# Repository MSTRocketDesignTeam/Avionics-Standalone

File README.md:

# Avionics-Standalone-PCB
Standalone Avionics Board

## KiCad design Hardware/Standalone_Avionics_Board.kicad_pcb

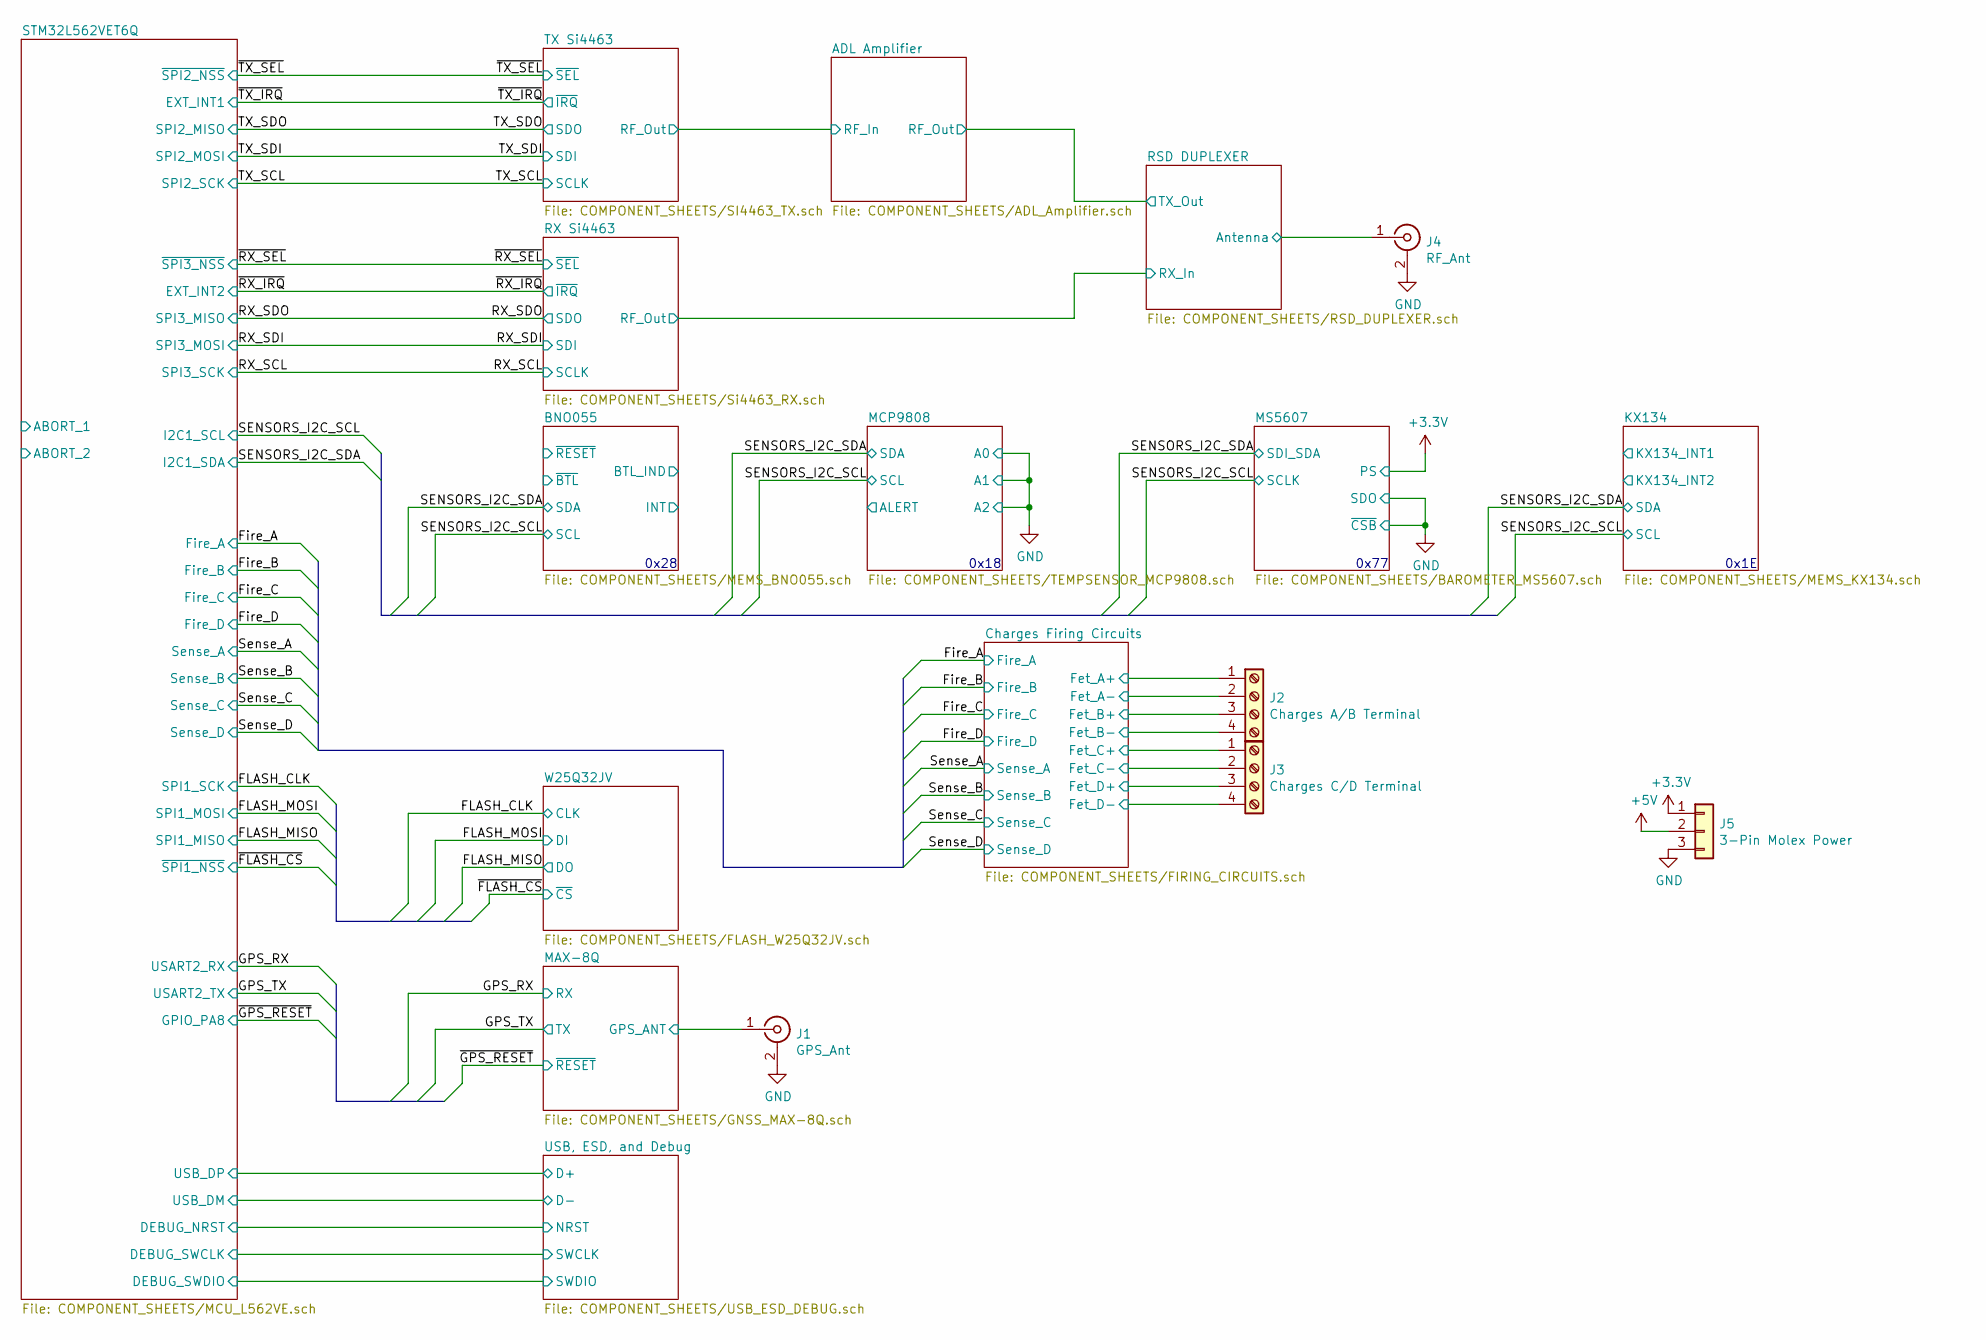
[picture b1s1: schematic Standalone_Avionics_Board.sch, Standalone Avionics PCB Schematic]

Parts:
J1: GPS_Ant; SMA_Amphenol_132134-11_Vertical
J2: Charges A/B Terminal; TerminalBlock_Phoenix_MKDS-1,5-4_1x04_P5.00mm_Horizontal
J3: Charges C/D Terminal; TerminalBlock_Phoenix_MKDS-1,5-4_1x04_P5.00mm_Horizontal
J4: RF_Ant; SMA_Amphenol_132134-11_Vertical
J5: 3-Pin Molex Power; Molex_KK-254_AE-6410-03A_1x03_P2.54mm_Vertical

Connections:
+3V3: J5.1; also elsewhere on the board
+5V: J5.2; also elsewhere on the board
/Charges Firing Circuits/Fet_A+: J2.1; also elsewhere on the board
/Charges Firing Circuits/Fet_A-: J2.2; also elsewhere on the board
/Charges Firing Circuits/Fet_B+: J2.3; also elsewhere on the board
/Charges Firing Circuits/Fet_B-: J2.4; also elsewhere on the board
/Charges Firing Circuits/Fet_C+: J3.1; also elsewhere on the board
/Charges Firing Circuits/Fet_C-: J3.2; also elsewhere on the board
/Charges Firing Circuits/Fet_D+: J3.3; also elsewhere on the board
/Charges Firing Circuits/Fet_D-: J3.4; also elsewhere on the board
/MAX-8Q/GPS_ANT: J1.1 (In); also elsewhere on the board
/RSD DUPLEXER/Antenna: J4.1 (In); also elsewhere on the board
GND: J1.2 (Ext), J4.2 (Ext), J5.3; also elsewhere on the board

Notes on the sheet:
0x1E
0x77
0x18
0x28

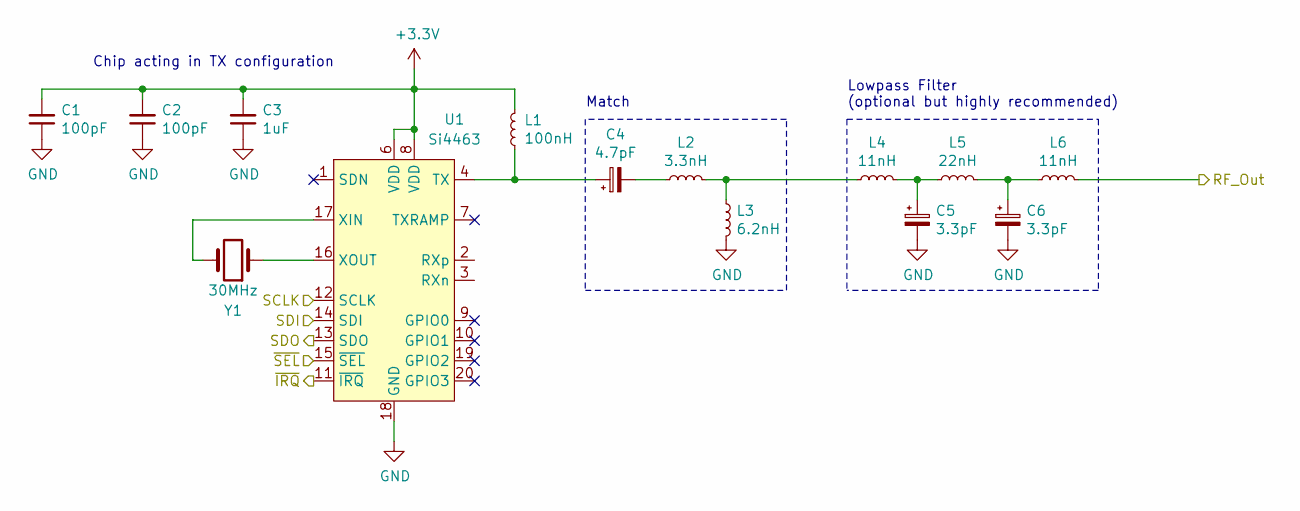
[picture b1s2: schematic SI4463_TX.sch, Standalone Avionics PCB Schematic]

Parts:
C1, C2: 100pF; C_0402_1005Metric
C3: 1uF; C_0402_1005Metric
C4: 4.7pF; C_0402_1005Metric
C5, C6: 3.3pF; C_0402_1005Metric
L1: 100nH; L_0402_1005Metric
L2: 3.3nH; L_0402_1005Metric
L3: 6.2nH; L_0402_1005Metric
L4, L6: 11nH; L_0402_1005Metric
L5: 22nH; L_0402_1005Metric
U1: Si4463; QFN-20-1EP_4x4mm_P0.5mm_EP2.5x2.5mm
Y1: 30MHz; Crystal_SMD_0603-2Pin_6.0x3.5mm

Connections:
+3V3: C1.2, C2.2, C3.2, L1.2, U1.6 (VDD), U1.8 (VDD); also elsewhere on the board
/ADL Amplifier/RF_In: L6.2; also elsewhere on the board
/TX_SCL: U1.12 (SCLK); also elsewhere on the board
/TX_SDI: U1.14 (SDI); also elsewhere on the board
/TX_SDO: U1.13 (SDO); also elsewhere on the board
/~TX_IRQ: U1.11 (~IRQ); also elsewhere on the board
/~TX_SEL: U1.15 (~SEL); also elsewhere on the board
GND: C1.1, C2.1, C3.1, C5.2, C6.2, L3.2, U1.18 (GND), U1.21 (GND); also elsewhere on the board
unnamed: C4.1, L1.1, U1.4 (TX)
unnamed: C4.2, L2.1
unnamed: C5.1, L4.2, L5.1
unnamed: C6.1, L5.2, L6.1
unnamed: L2.2, L3.1, L4.1
unnamed: U1.16 (XOUT), Y1.1
unnamed: U1.17 (XIN), Y1.2

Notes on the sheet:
Chip acting in TX configuration
Lowpass Filter (optional but highly recommended)
Match

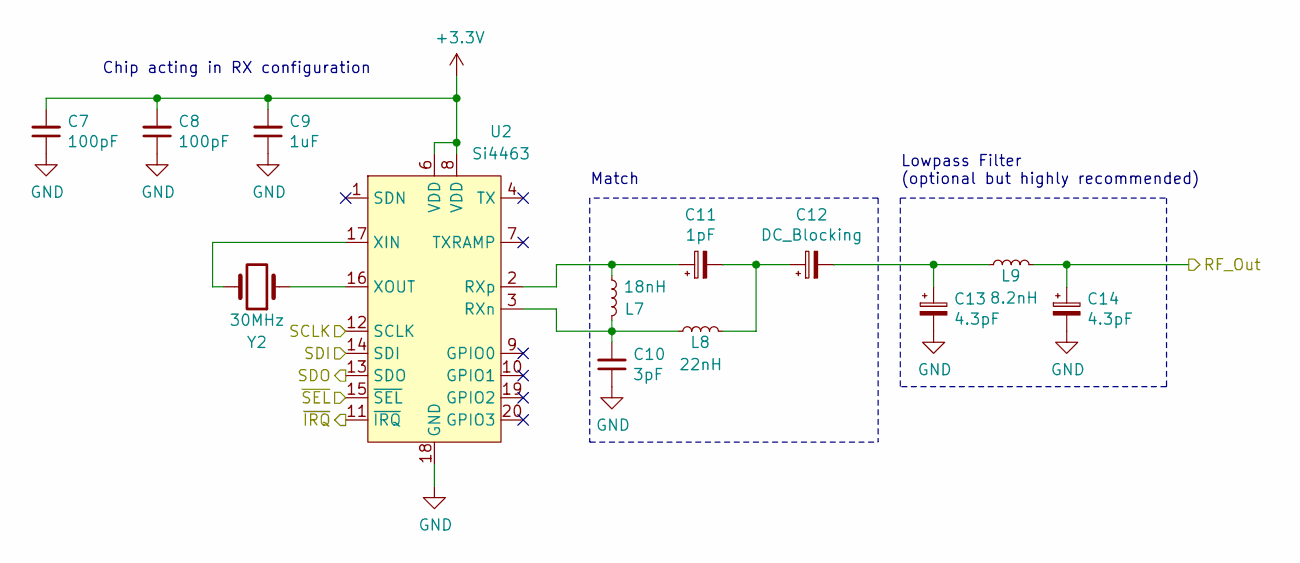
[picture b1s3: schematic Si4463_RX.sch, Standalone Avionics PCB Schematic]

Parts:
C7, C8: 100pF; C_0402_1005Metric
C9: 1uF; C_0402_1005Metric
C10: 3pF; C_0402_1005Metric
C11: 1pF; C_0402_1005Metric
C12: DC_Blocking; C_0402_1005Metric
C13, C14: 4.3pF; C_0402_1005Metric
L7: 18nH; L_0402_1005Metric
L8: 22nH; L_0402_1005Metric
L9: 8.2nH; L_0402_1005Metric
U2: Si4463; QFN-20-1EP_4x4mm_P0.5mm_EP2.5x2.5mm
Y2: 30MHz; Crystal_SMD_0603-2Pin_6.0x3.5mm

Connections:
+3V3: C7.2, C8.2, C9.2, U2.6 (VDD), U2.8 (VDD); also elsewhere on the board
/RX Si4463/RF_Out: C14.1, L9.2; also elsewhere on the board
/RX_SCL: U2.12 (SCLK); also elsewhere on the board
/RX_SDI: U2.14 (SDI); also elsewhere on the board
/RX_SDO: U2.13 (SDO); also elsewhere on the board
/~RX_IRQ: U2.11 (~IRQ); also elsewhere on the board
/~RX_SEL: U2.15 (~SEL); also elsewhere on the board
GND: C7.1, C8.1, C9.1, C10.1, C13.2, C14.2, U2.18 (GND), U2.21 (GND); also elsewhere on the board
unnamed: C10.2, L7.2, L8.1, U2.3 (RXn)
unnamed: C11.1, L7.1, U2.2 (RXp)
unnamed: C11.2, C12.1, L8.2
unnamed: C12.2, C13.1, L9.1
unnamed: U2.16 (XOUT), Y2.1
unnamed: U2.17 (XIN), Y2.2

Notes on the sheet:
Chip acting in RX configuration
Lowpass Filter (optional but highly recommended)
Match

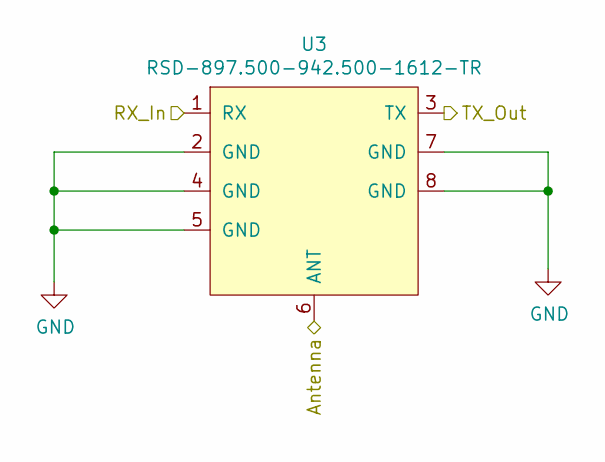
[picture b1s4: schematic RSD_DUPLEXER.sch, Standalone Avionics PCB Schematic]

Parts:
U3: RSD-897.500-942.500-1612-TR

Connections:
/ADL Amplifier/RF_Out: U3.3 (TX); also elsewhere on the board
/RSD DUPLEXER/Antenna: U3.6 (ANT); also elsewhere on the board
/RX Si4463/RF_Out: U3.1 (RX); also elsewhere on the board
GND: U3.2 (GND), U3.4 (GND), U3.5 (GND), U3.7 (GND), U3.8 (GND); also elsewhere on the board

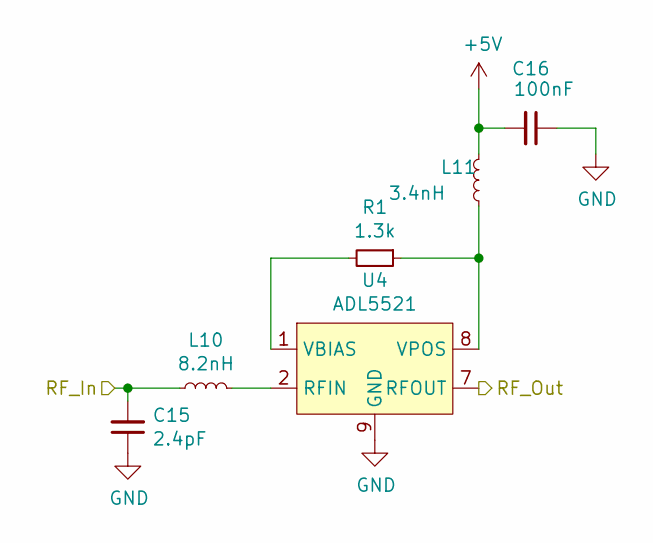
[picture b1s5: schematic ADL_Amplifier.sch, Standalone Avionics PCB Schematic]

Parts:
C15: 2.4pF; C_0402_1005Metric
C16: 100nF; C_0402_1005Metric
L10: 8.2nH; L_0402_1005Metric
L11: 3.4nH; L_0402_1005Metric
R1: 1.3k; R_0402_1005Metric
U4: ADL5521; LFCSP-8-1EP_3x2mm_P0.5mm_EP1.6x1.65mm

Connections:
+5V: C16.2, L11.2; also elsewhere on the board
/ADL Amplifier/RF_In: C15.2, L10.1; also elsewhere on the board
/ADL Amplifier/RF_Out: U4.7 (RFOUT); also elsewhere on the board
GND: C15.1, C16.1, U4.9 (GND); also elsewhere on the board
unnamed: L10.2, U4.2 (RFIN)
unnamed: L11.1, R1.1, U4.8 (VPOS)
unnamed: R1.2, U4.1 (VBIAS)

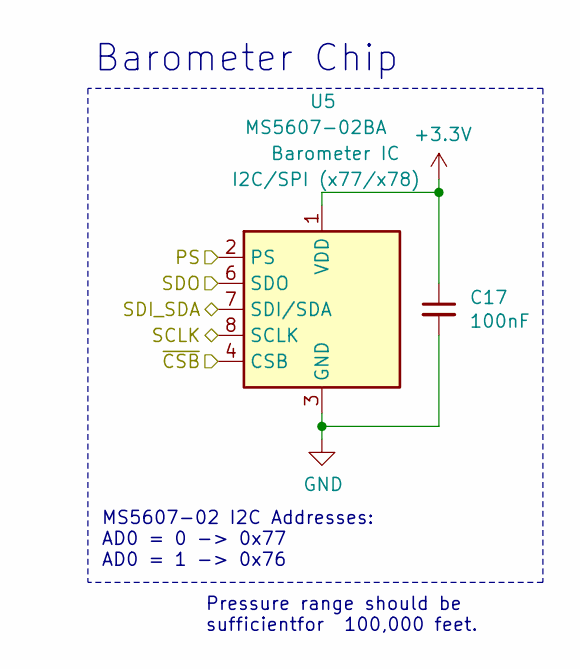
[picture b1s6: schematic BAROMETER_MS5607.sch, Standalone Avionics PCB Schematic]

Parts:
C17: 100nF; C_0402_1005Metric
U5: MS5607-02BA; LGA-8_3x5mm_P1.25mm

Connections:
+3V3: C17.1, U5.1 (VDD), U5.2 (PS); also elsewhere on the board
/SENSORS_I2C_SCL: U5.8 (SCLK); also elsewhere on the board
/SENSORS_I2C_SDA: U5.7 (SDI/SDA); also elsewhere on the board
GND: C17.2, U5.3 (GND), U5.4 (CSB), U5.5 (CSB), U5.6 (SDO); also elsewhere on the board

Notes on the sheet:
Barometer Chip
MS5607-02 I2C Addresses: AD0 = 0 -> 0x77 AD0 = 1 -> 0x76
Pressure range should be sufficientfor ~ 100,000 feet.

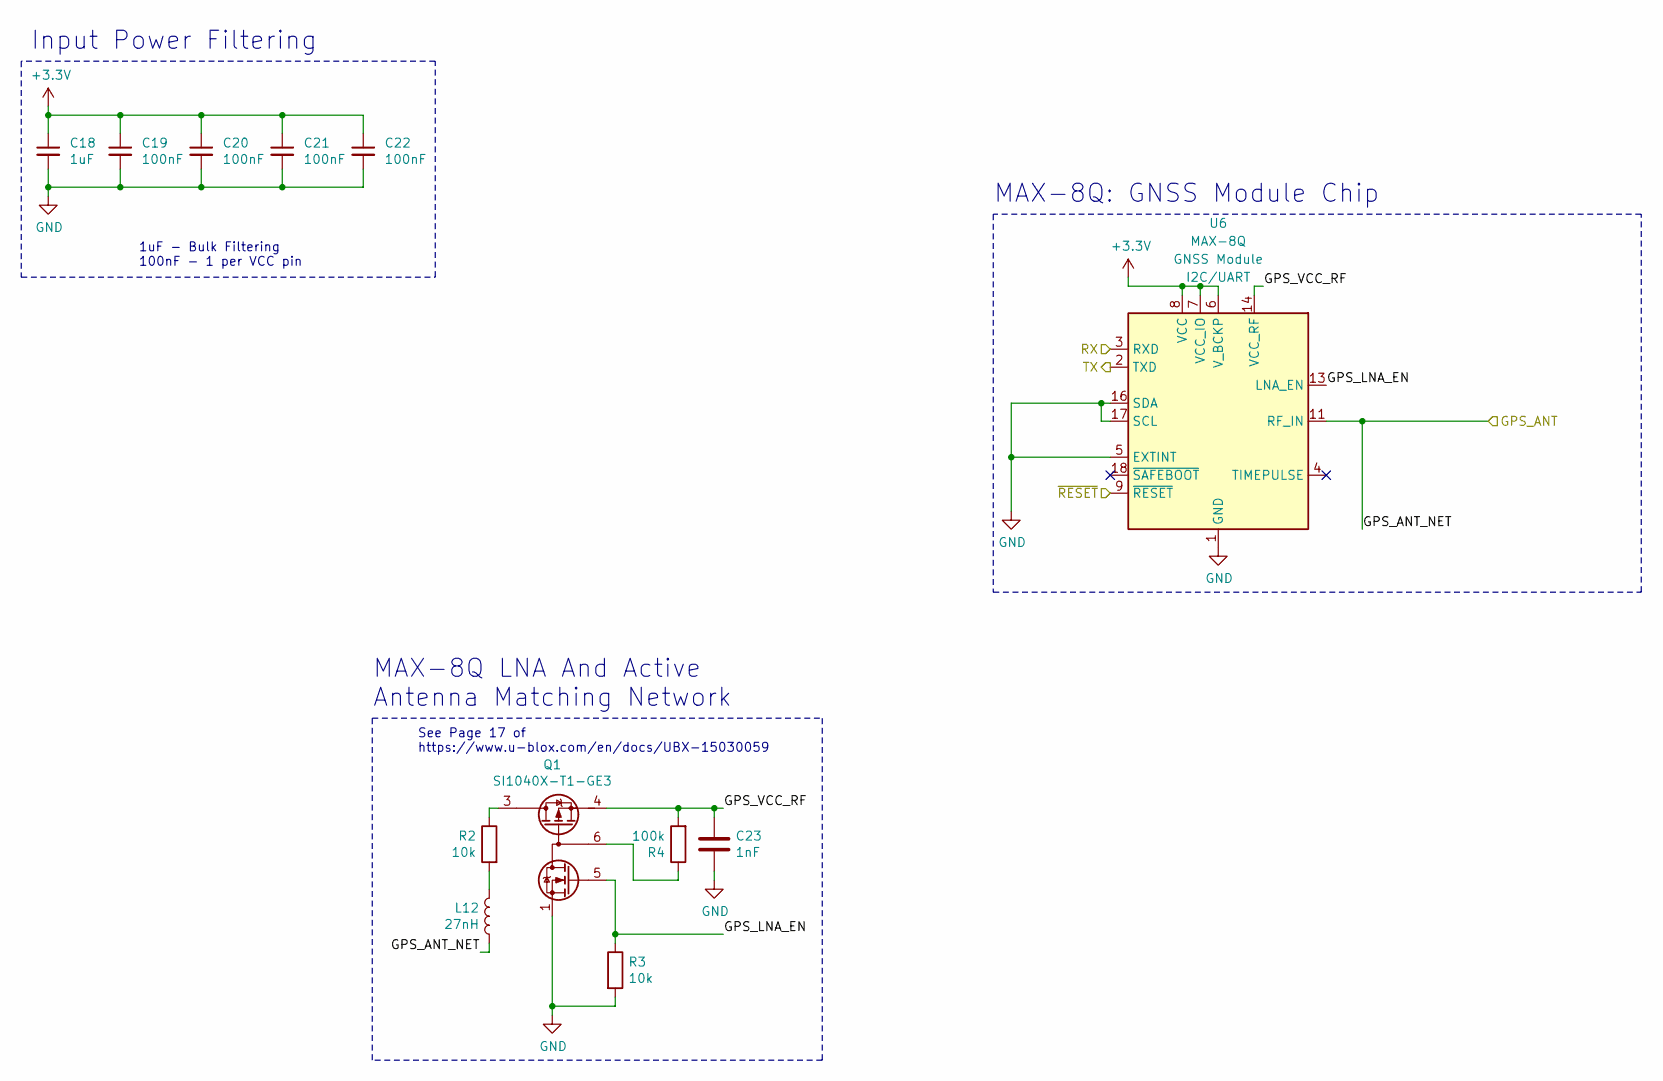
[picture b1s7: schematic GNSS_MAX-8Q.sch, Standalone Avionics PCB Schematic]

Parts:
C18: 1uF; C_0402_1005Metric
C19, C20, C21, C22: 100nF; C_0402_1005Metric
C23: 1nF; C_0402_1005Metric
L12: 27nH; L_0402_1005Metric
Q1: SI1040X-T1-GE3; SOT-563
R2, R3: 10k; R_0402_1005Metric
R4: 100k; R_0402_1005Metric
U6: MAX-8Q; ublox_MAX

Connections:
+3V3: C18.1, C19.1, C20.1, C21.1, C22.1, U6.6 (V_BCKP), U6.7 (VCC_IO), U6.8 (VCC); also elsewhere on the board
/GPS_RX: U6.3 (RXD); also elsewhere on the board
/GPS_TX: U6.2 (TXD); also elsewhere on the board
/MAX-8Q/GPS_ANT: L12.2, U6.11 (RF_IN); also elsewhere on the board
/MAX-8Q/GPS_LNA_EN: Q1.5 (G1), R3.1, U6.13 (LNA_EN)
/MAX-8Q/GPS_VCC_RF: C23.1, Q1.4 (S2), R4.2, U6.14 (VCC_RF)
/~GPS_RESET: U6.9 (~RESET); also elsewhere on the board
GND: C18.2, C19.2, C20.2, C21.2, C22.2, C23.2, Q1.1 (S1), R3.2, U6.1 (GND), U6.5 (EXTINT), U6.10 (GND), U6.12 (GND), U6.16 (SDA), U6.17 (SCL); also elsewhere on the board
unnamed: L12.1, R2.2
unnamed: Q1.2 (D2), Q1.3 (D2), R2.1
unnamed: Q1.6 (D1), R4.1

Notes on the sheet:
See Page 17 of https://www.u-blox.com/en/docs/UBX-15030059
MAX-8Q: GNSS Module Chip
1uF - Bulk Filtering 100nF - 1 per VCC pin
Input Power Filtering
MAX-8Q LNA And Active Antenna Matching Network

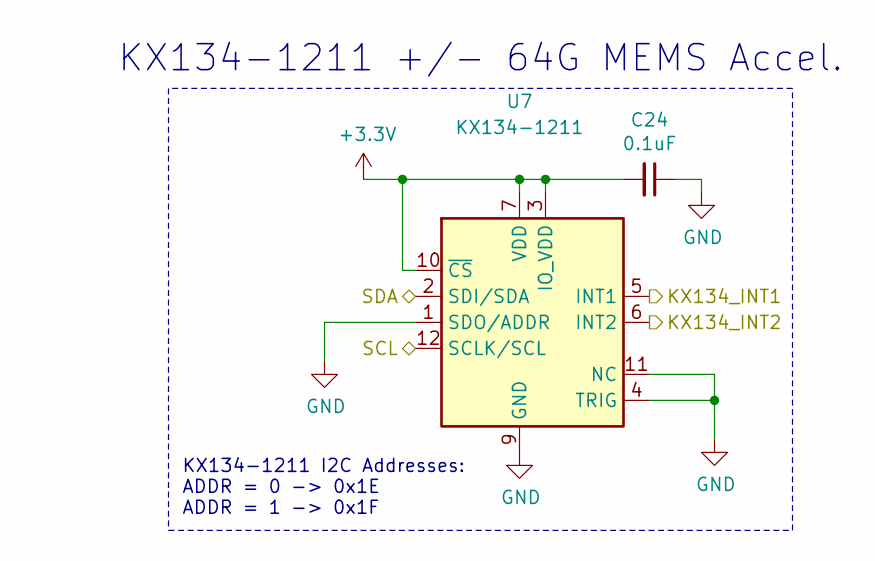
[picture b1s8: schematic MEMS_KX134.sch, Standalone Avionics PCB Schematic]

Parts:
C24: 0.1uF; C_0402_1005Metric
U7: KX134-1211; LGA-12_2x2mm_P0.5mm

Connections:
+3V3: C24.2, U7.3 (IO_VDD), U7.7 (VDD), U7.10 (~CS); also elsewhere on the board
/KX134/KX134_INT1: U7.5 (INT1)
/KX134/KX134_INT2: U7.6 (INT2)
/SENSORS_I2C_SCL: U7.12 (SCLK/SCL); also elsewhere on the board
/SENSORS_I2C_SDA: U7.2 (SDI/SDA); also elsewhere on the board
GND: C24.1, U7.1 (SDO/ADDR), U7.4 (TRIG), U7.9 (GND), U7.11 (NC); also elsewhere on the board

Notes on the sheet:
KX134-1211 I2C Addresses: ADDR = 0 -> 0x1E ADDR = 1 -> 0x1F
KX134-1211 +/- 64G MEMS Accel.

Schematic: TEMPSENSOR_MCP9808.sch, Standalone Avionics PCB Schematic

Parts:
C25: 100nF; C_0402_1005Metric
U8: MCP9808_MSOP; MSOP-8-1EP_3x3mm_P0.65mm_EP1.68x1.88mm

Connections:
+3V3: C25.1, U8.8 (VDD); also elsewhere on the board
/MCP9808/ALERT: U8.3 (Alert)
/SENSORS_I2C_SCL: U8.2 (SCL); also elsewhere on the board
/SENSORS_I2C_SDA: U8.1 (SDA); also elsewhere on the board
GND: C25.2, U8.4 (GND), U8.5 (A2), U8.6 (A1), U8.7 (A0), U8.9 (EP/GND); also elsewhere on the board

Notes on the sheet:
Temp Sensor
MCP9804 I2C Addresses: |A2 A1 A0| 0011|X X X |

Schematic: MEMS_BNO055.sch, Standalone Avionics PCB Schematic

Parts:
C26, C27, C28, C29: 0.1uF; C_0402_1005Metric
U9: BNO055; LGA-28_5.2x3.8mm_P0.5mm
Y3: 32.768kHz; Crystal_SMD_0603-2Pin_6.0x3.5mm

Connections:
+3V3: C26.2, U9.3 (VDD), U9.28 (VDDIO); also elsewhere on the board
/BNO055/BTL_IND: U9.10 (BL_IND)
/BNO055/INT: U9.14 (INT)
/BNO055/~BTL: U9.4 (~BOOT_LOAD_PIN)
/BNO055/~RESET: U9.11 (~RESET)
/SENSORS_I2C_SCL: U9.19 (COM1); also elsewhere on the board
/SENSORS_I2C_SDA: U9.20 (COM0); also elsewhere on the board
GND: C26.1, C27.2, C28.1, C29.2, U9.2 (GND), U9.5 (PS1), U9.6 (PS0), U9.15 (GNDIO), U9.16 (GNDIO), U9.17 (COM3), U9.18 (COM2), U9.25 (GNDIO); also elsewhere on the board
unnamed: C27.1, U9.9 (CAP)
unnamed: C28.2, U9.26 (XOUT32), Y3.1
unnamed: C29.1, U9.27 (XIN32), Y3.2

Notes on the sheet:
BNO 055 I2C Addresses: COM3 = 0 -> 0x28 COM3 = 1 -> 0x29
BNO 055 9-Axis MEMS Chip

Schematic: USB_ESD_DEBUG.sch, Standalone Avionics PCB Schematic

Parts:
C30: 100nF; C_0402_1005Metric
C31: 0.1uF; C_0402_1005Metric
C32: 1uF; C_0402_1005Metric
D1: D_Schottky_Small; D_0402_1005Metric
FB1: Ferrite_Bead_Small; C_0402_1005Metric
J6: 10118192-0001LF; USB_Micro-B_Wuerth_614105150721_Vertical; MPN 10118192-0001LF; Digi-Key_PN 609-4613-1-ND
J7: ARM 10 Pin; PinHeader_2x05_P2.54mm_Vertical
R5: 390Ω; R_0402_1005Metric
R6: 240Ω; R_0402_1005Metric
U10: LM317T; TO-220-3_Vertical; MPN LM317T; Digi-Key_PN 497-1575-5-ND
U11: USBLC6-2SC6; SOT-23-6

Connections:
+3V3: C32.1, J7.1, R6.1, U10.2 (OUT); also elsewhere on the board
+5V: C31.1, D1.1 (K), U10.3 (IN), U11.5 (VBUS); also elsewhere on the board
/STM32L562VET6Q/DEBUG_NRST: C30.1, J7.10; also elsewhere on the board
/STM32L562VET6Q/DEBUG_SWCLK: J7.4; also elsewhere on the board
/STM32L562VET6Q/DEBUG_SWDIO: J7.2; also elsewhere on the board
/USB, ESD, and Debug/D+: U11.1 (I/O1); also elsewhere on the board
/USB, ESD, and Debug/D-: U11.3 (I/O2); also elsewhere on the board
/USB, ESD, and Debug/USB_CONN_D+: J6.3 (D+), U11.6 (I/O1)
/USB, ESD, and Debug/USB_CONN_D-: J6.2 (D-), U11.4 (I/O2)
GND: C30.2, C31.2, C32.2, J6.5 (GND), J7.3, J7.5, J7.9, R5.2, U11.2 (GND); also elsewhere on the board
unnamed: D1.2 (A), FB1.1
unnamed: FB1.2, J6.1 (VBUS)
unnamed: R5.1, R6.2, U10.1 (ADJ)

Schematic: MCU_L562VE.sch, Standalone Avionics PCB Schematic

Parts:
C35: 1uF; C_0402_1005Metric
C36, C37, C38, C39, C40, C41, C42, C43, C44: 100nF; C_0402_1005Metric
D2, D3, D4, D5, D6: LED; LED_0402_1005Metric
R7, R8, R9, R10, R11: 100Ω; R_0402_1005Metric
R13, R14: 4.7k; R_0402_1005Metric
U12: STM32L562VET; LQFP-100_14x14mm_P0.5mm

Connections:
+3V3: C35.1, C36.1, C37.1, C38.1, C39.1, C40.1, C41.1, C42.1, C43.1, C44.1, R13.2, R14.2, U12.6 (VBAT), U12.11 (VDD), U12.21 (VDDA), U12.27 (VDD), U12.46 (VDDSMPS), U12.51 (VDD), U12.73 (VDDUSB), U12.75 (VDD), U12.100 (VDD); also elsewhere on the board
/FLASH_CLK: U12.29 (PA5); also elsewhere on the board
/FLASH_MISO: U12.30 (PA6); also elsewhere on the board
/FLASH_MOSI: U12.31 (PA7); also elsewhere on the board
/Fire_A: U12.57 (PD10); also elsewhere on the board
/Fire_B: U12.59 (PD12); also elsewhere on the board
/Fire_C: U12.90 (PB4); also elsewhere on the board
/Fire_D: U12.88 (PD7); also elsewhere on the board
/GPS_RX: U12.69 (PA10); also elsewhere on the board
/GPS_TX: U12.68 (PA9); also elsewhere on the board
/RX_SCL: U12.78 (PC10); also elsewhere on the board
/RX_SDI: U12.80 (PC12); also elsewhere on the board
/RX_SDO: U12.79 (PC11); also elsewhere on the board
/SENSORS_I2C_SCL: R13.1, U12.95 (PB8); also elsewhere on the board
/SENSORS_I2C_SDA: R14.1, U12.96 (PB9); also elsewhere on the board
/STM32L562VET6Q/ABORT_1: U12.2 (PE3)
/STM32L562VET6Q/ABORT_2: U12.1 (PE2)
/STM32L562VET6Q/DEBUG_NRST: U12.14 (NRST); also elsewhere on the board
/STM32L562VET6Q/DEBUG_SWCLK: U12.76 (PA14); also elsewhere on the board
/STM32L562VET6Q/DEBUG_SWDIO: U12.72 (PA13); also elsewhere on the board
/Sense_A: U12.58 (PD11); also elsewhere on the board
/Sense_B: U12.60 (PD13); also elsewhere on the board
/Sense_C: U12.89 (PB3); also elsewhere on the board
/Sense_D: U12.87 (PD6); also elsewhere on the board
/TX_SCL: U12.52 (PB13); also elsewhere on the board
/TX_SDI: U12.54 (PB15); also elsewhere on the board
/TX_SDO: U12.53 (PB14); also elsewhere on the board
/USB, ESD, and Debug/D+: U12.71 (PA12); also elsewhere on the board
/USB, ESD, and Debug/D-: U12.70 (PA11); also elsewhere on the board
/~FLASH_CS: U12.32 (PB0); also elsewhere on the board
/~GPS_RESET: U12.67 (PA8); also elsewhere on the board
/~RX_IRQ: U12.64 (PC7); also elsewhere on the board
/~RX_SEL: U12.28 (PA4); also elsewhere on the board
/~TX_IRQ: U12.63 (PC6); also elsewhere on the board
/~TX_SEL: U12.81 (PD0); also elsewhere on the board
GND: C35.2, C36.2, C37.2, C38.2, C39.2, C40.2, C41.2, C42.2, C43.2, C44.2, D2.1 (K), D3.1 (K), D4.1 (K), D5.1 (K), D6.1 (K), U12.10 (VSS), U12.26 (VSS), U12.49 (VSS), U12.74 (VSS), U12.98 (VSS); also elsewhere on the board
unnamed: D2.2 (A), R7.2
unnamed: D3.2 (A), R8.2
unnamed: D4.2 (A), R9.2
unnamed: D5.2 (A), R10.2
unnamed: D6.2 (A), R11.2
unnamed: R7.1, U12.82 (PD1)
unnamed: R8.1, U12.83 (PD2)
unnamed: R9.1, U12.84 (PD3)
unnamed: R10.1, U12.85 (PD4)
unnamed: R11.1, U12.86 (PD5)

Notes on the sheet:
Microcontroller Input Power Filtering
1uF - Bulk Filtering 100nF - 1 per VCC pin
PVD_IN is the Power Voltage Dropout pin, used to detect and respond to brownout conditions.
I2C1 Pullup Resistors

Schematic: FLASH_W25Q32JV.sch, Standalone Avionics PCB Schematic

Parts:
C45: 100nF; C_0402_1005Metric
U13: W25Q32JVSS; SOIC-8_5.23x5.23mm_P1.27mm

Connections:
+3V3: C45.1, U13.8 (VCC); also elsewhere on the board
/FLASH_CLK: U13.6 (CLK); also elsewhere on the board
/FLASH_MISO: U13.2 (DO(IO1)); also elsewhere on the board
/FLASH_MOSI: U13.5 (DI(IO0)); also elsewhere on the board
/~FLASH_CS: U13.1 (~CS); also elsewhere on the board
GND: C45.2, U13.3 (IO2), U13.4 (GND), U13.7 (IO3); also elsewhere on the board

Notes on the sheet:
Flash Storage Chip

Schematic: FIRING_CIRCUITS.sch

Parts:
C46, C47, C48, C49: CP1_Small; C_0402_1005Metric
Q2, Q3: SI7232DN-T1-GE3; SI7232DNT1GE3; Mouser Part Number 781-SI7232DN-GE3
R15, R16, R17, R18: 1k; R_0402_1005Metric
R19, R20, R21, R22: 10k; R_0402_1005Metric
R23, R24, R27, R28: 10; R_0402_1005Metric
R25, R26, R29, R30: 0.25; R_0402_1005Metric
R31, R32, R33, R34: 100k; R_0402_1005Metric
R35, R36, R37, R38: 27k; R_0402_1005Metric

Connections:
+5V: R23.2, R24.2, R27.2, R28.2; also elsewhere on the board
/Charges Firing Circuits/Fet_A+: Q2.7 (D1_1), Q2.8 (D1_2), Q2.9 (D1_3), Q2.10 (D1_4), Q2.11 (D1_5), Q2.15 (D1_6), R31.2; also elsewhere on the board
/Charges Firing Circuits/Fet_A-: R25.1; also elsewhere on the board
/Charges Firing Circuits/Fet_B+: Q2.5 (D2_1), Q2.6 (D2_2), Q2.12 (D2_3), Q2.13 (D2_4), Q2.14 (D2_5), Q2.16 (D2_6), R32.2; also elsewhere on the board
/Charges Firing Circuits/Fet_B-: R26.1; also elsewhere on the board
/Charges Firing Circuits/Fet_C+: Q3.7 (D1_1), Q3.8 (D1_2), Q3.9 (D1_3), Q3.10 (D1_4), Q3.11 (D1_5), Q3.15 (D1_6), R33.2; also elsewhere on the board
/Charges Firing Circuits/Fet_C-: R29.1; also elsewhere on the board
/Charges Firing Circuits/Fet_D+: Q3.5 (D2_1), Q3.6 (D2_2), Q3.12 (D2_3), Q3.13 (D2_4), Q3.14 (D2_5), Q3.16 (D2_6), R34.2; also elsewhere on the board
/Charges Firing Circuits/Fet_D-: R30.1; also elsewhere on the board
/Fire_A: R15.2; also elsewhere on the board
/Fire_B: R16.2; also elsewhere on the board
/Fire_C: R17.2; also elsewhere on the board
/Fire_D: R18.2; also elsewhere on the board
/Sense_A: R31.1, R35.2; also elsewhere on the board
/Sense_B: R32.1, R36.2; also elsewhere on the board
/Sense_C: R33.1, R37.2; also elsewhere on the board
/Sense_D: R34.1, R38.2; also elsewhere on the board
GND: C46.2, C47.2, C48.2, C49.2, Q2.1 (S1), Q2.3 (S2), Q3.1 (S1), Q3.3 (S2), R19.1, R20.1, R21.1, R22.1, R35.1, R36.1, R37.1, R38.1; also elsewhere on the board
unnamed: C46.1, R23.1, R25.2
unnamed: C47.1, R24.1, R26.2
unnamed: C48.1, R27.1, R29.2
unnamed: C49.1, R28.1, R30.2
unnamed: Q2.2 (G1), R15.1, R19.2
unnamed: Q2.4 (G2), R16.1, R20.2
unnamed: Q3.2 (G1), R17.1, R21.2
unnamed: Q3.4 (G2), R18.1, R22.2

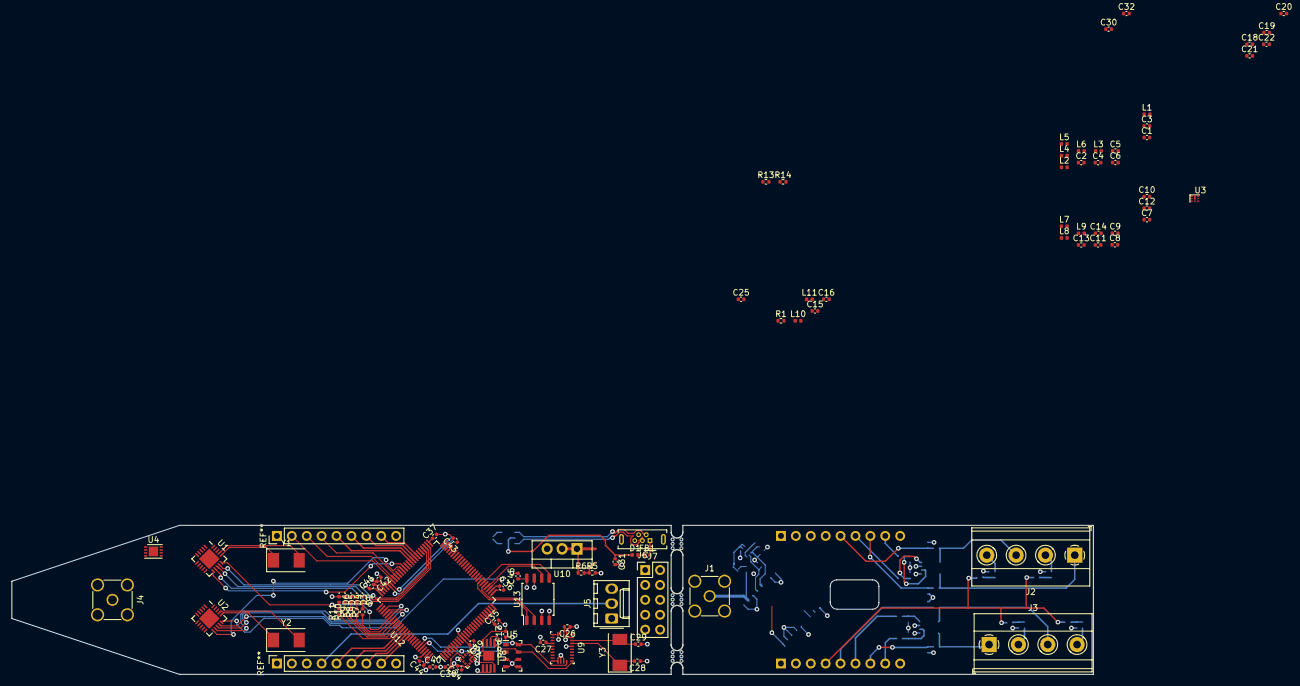
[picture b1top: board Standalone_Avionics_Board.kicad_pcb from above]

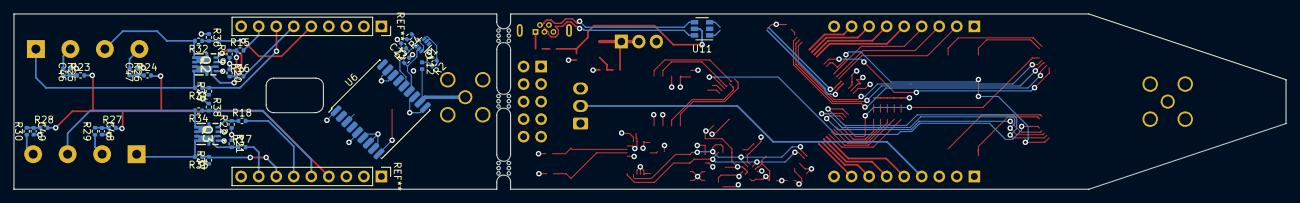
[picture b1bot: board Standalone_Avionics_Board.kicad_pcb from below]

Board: 4 copper layers, 184.3 x 25.4 mm, 132 parts (38 on the bottom side), 95 nets.

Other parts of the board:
mouse-bite-2mm-slot, mouse-bite-2mm-slot#2, mouse-bite-2mm-slot#3: VAL**; mouse-bite-2mm-slot

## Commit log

2021-12-08 Initial Schematic
    Used component sheets from Data Collection, Telemetry, and Pyro Charges Boards.
    Still needs power section.
2021-12-08 Annotated and Assigned Footprints
2021-12-08 Corrected some footprint associations
2021-12-08 Initial component placement on board
2021-12-08 Replaced 2x 4pole terminal blocks with 1x 8pole
2021-12-09 Added status LEDs to MCU
2021-12-09 Added status LEDs to pcb
2021-12-10 Played with board sizes
2021-12-10 Removed microcontroller clock to save space
2021-12-11 Added traces for I2C sensors
2021-12-11 Forced addresses for I2C devices
2021-12-11 Board Layout Progress
2021-12-11 Routed ESD protection chip for USB
    I really hate how this connects, I made the chip go on the bottom of the board but I really don't want to
2021-12-11 All chips on layout besides passives
2021-12-12 Added Mouse Bites
2021-12-12 Adjusted GPS module position
2021-12-12 Connected SPI lines to RX/TX chips
    Really need to figure out layout for crystals
